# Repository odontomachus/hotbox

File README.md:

# hotbox

A pid temperature controller with a serial client used in a hotbox for ski waxing.

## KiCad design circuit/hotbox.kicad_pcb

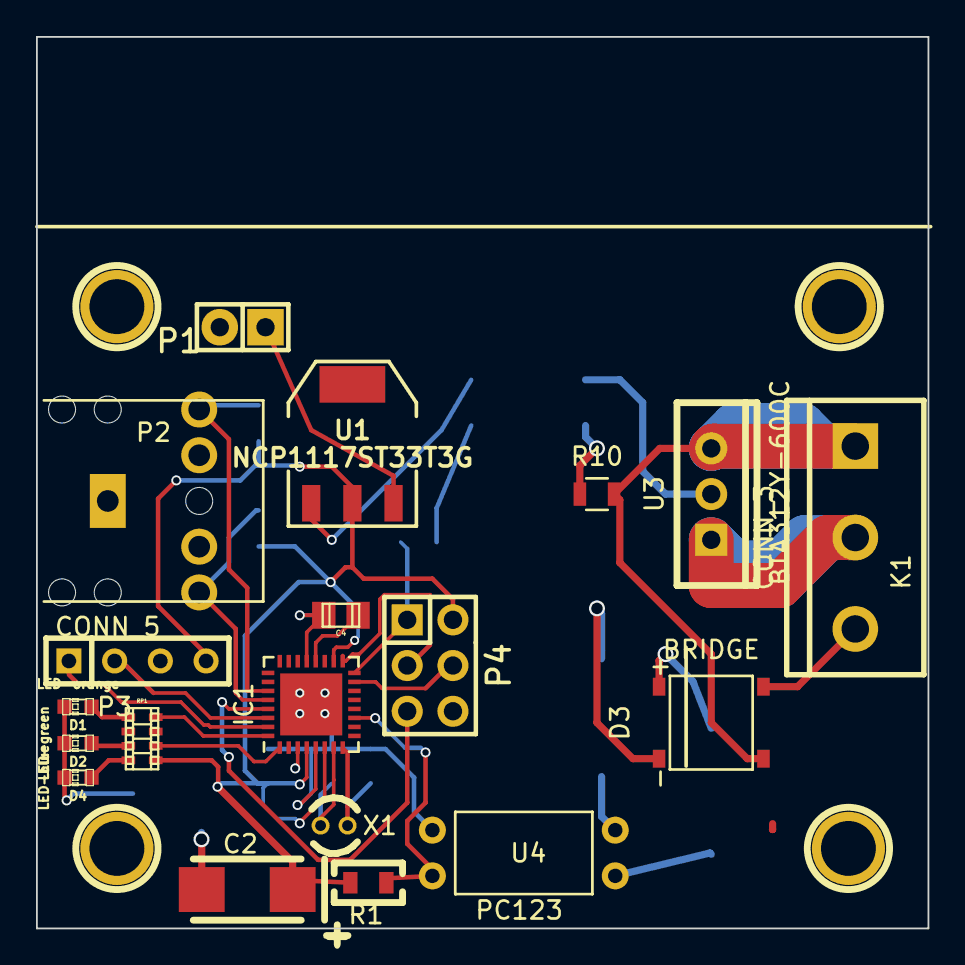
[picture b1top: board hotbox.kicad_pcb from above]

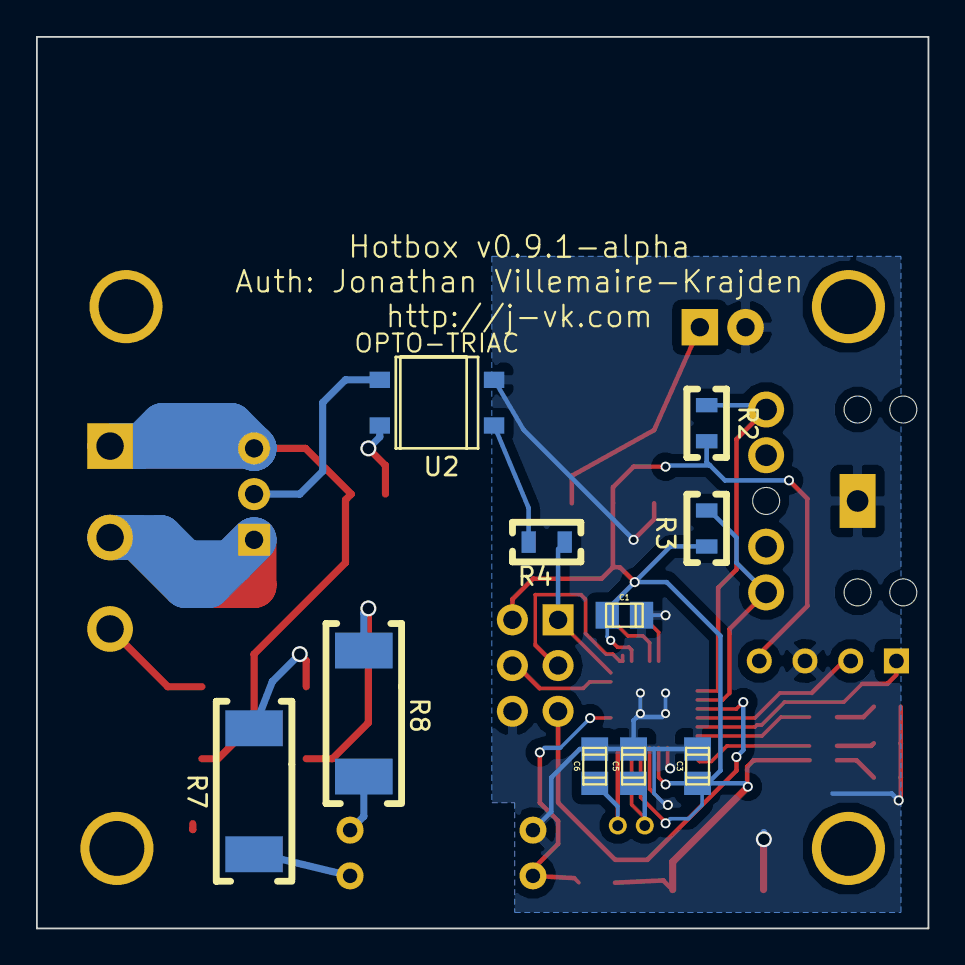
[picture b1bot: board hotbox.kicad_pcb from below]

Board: 2 copper layers, 49.5 x 49.5 mm, 33 parts (10 on the bottom side), 30 nets.

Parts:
1PIN, 1PIN#2, 1PIN#3, 1PIN#4: P***; 1pin
C1: C; c_0805
C2: 220uF; TantalC_SizeC_EIA-6032_Reflow
C3: 220uF; c_0805
C4: 0.1uF; c_0805
C5, C6: 12pF; c_0805
D1: LED-orange; LED-0603
D2: LED-green; LED-0603
D3: BRIDGE; RECTIFIER_BRIDGE
D4: LED-blue; LED-0603
IC1: ATMEGA48A-M; QFN-32-1EP_5x5mm_Pitch0.5mm
K1: CONN_3; bornier3
P1: CONN_2; Socket_Strip_Straight_1x02
P2: CONN_5; CONN_AUDIO_JACK
P3: CONN_4; SIL-4
P4: CONN_3X2; Socket_Strip_Straight_2x03
R1: 4.7kR; Resistor_SMD0805_ReflowWave
R2, R3, R4: R; Resistor_SMD0805_ReflowWave
R7, R8: 22kR; Resistor_SMD2512_ReflowWave
R10: 330R; R_0805
RP1: 82R; r_cat16-4
U1: NCP1117ST33T3G; SOT223
U2: OPTO-TRIAC; SOP-4
U3: BTA312Y-600C; TO220_VERT
U4: PC123; DIP4F
X1: CRYSTAL; Crystal_Round_Vertical_3mm

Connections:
+3V3: C1.2, C2.1, C3.2, IC1.4, IC1.6, IC1.18, P3.4, P4.6, R1.2, R2.2, R3.2, RP1.1, U1.2
/TH1: IC1.27, P2.2, R2.1
/TH2: IC1.28, P2.5, R3.1
/live: D3.2, K1.1, R10.2, U3.2
/load: K1.2, U3.1
/neutral: D3.4, K1.3
/zc: IC1.11, R1.1, U4.4
GND: C1.1, C2.2, C3.1, C4.1, C5.1, C6.1, D1.2, D2.2, D4.2, IC1.3, IC1.5, IC1.21, P1.2, P2.1, P3.3, P4.4, U1.1, U2.2, U4.3
unnamed: C4.2, IC1.20
unnamed: C5.2, IC1.7, X1.1
unnamed: C6.2, IC1.8, X1.2
unnamed: D1.1, RP1.5
unnamed: D2.1, RP1.7
unnamed: D3.1, R8.1
unnamed: D3.3, R7.1
unnamed: D4.1, RP1.8
unnamed: IC1.1, RP1.2
unnamed: IC1.15, P4.5
unnamed: IC1.16, P4.1, R4.2
unnamed: IC1.17, P4.2
unnamed: IC1.29, P4.3
unnamed: IC1.30, P3.2
unnamed: IC1.31, P3.1
unnamed: IC1.32, RP1.4
unnamed: P1.1, U1.3
unnamed: R4.1, U2.1
unnamed: R7.2, U4.1
unnamed: R8.2, U4.2
unnamed: R10.1, U2.6
unnamed: U2.4, U3.3

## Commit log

2015-03-11 Adding c code.
2015-03-13 First working.
2015-03-22 Fixed loop bug and temp parameter matching.
2015-03-22 Fixed byte readings for signed bytes.
2015-03-22 Reset default time to 6 hours.
2015-03-22 Using xtal and client fixes for on/off
2015-03-22 Added configure function.
2015-03-22 Added keys.
2015-03-22 Changed port.
2015-03-22 Fixed merge errors.
2015-03-22 Added output.
2015-03-22 Open file in write.
2015-04-01 Updated communication protocol, added messages.
2015-04-01 Leaner messages.
2015-04-01 Tk interface beggining.
2015-04-01 interface shell.
2015-04-01 Moved config to separate file.
2015-04-03 Fix for null char string in transmit.
2015-04-03 Working client controls.
2015-04-04 Added set temp and time to status messages.
2015-04-04 functional save button.
2015-04-04 Status bar for heating intensity.
2015-04-04 Live graphing of data.
2015-04-04 Fixed duplicate temp line on restart.
2015-04-04 Added labels to axes and legend.
2015-04-04 Reset to atmega48.
2015-04-04 Info box display, reset to windows port by default.
2015-04-05 Added connection status.
2015-04-05 Missing header file, licence
2015-04-05 Added .gitignore.
2015-04-14 Time tracking now uses long (>18h) and use struct for conversions.
2015-04-14 Formatting changes in config.
2015-05-19 Changed legend position and made draggable.
2015-05-19 Added tight_layout to graph."
2015-05-28 Added partial circuit pcb.
2015-05-28 Alpha version of complete pcb, untested.
2015-05-29 Switched to 5x5cm for seeedstudio.
2015-05-29 Move traces further from edges.
2015-05-29 Moved gerber to subfolder.
2015-05-31 5x5cm version.
2015-06-12 Simplifid schematics removed snubber circuit (not necessary with BTA312Y).
2015-10-14 Helper script to figure out thermistor values.
2015-10-15 pcb uses mega48.
2015-10-15 Starting changes towards pcb code.
2017-09-22 Adding requirements.
